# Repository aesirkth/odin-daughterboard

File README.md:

# daughterboard
Daughterboard design notes:

DB circle dimension: 60 mm, up to 75 mm

Include space for 4-5 spacers around edge of PCB

On one of the sides, add space for the header (pin stack) where all the output connections will go to the rest of the electronics. 

Include through holes for the 2 wires to the battery, (Vcc and GND)

AWG 16 cables (order BLACK cables for GND, RED for Vcc)

2 Inputs from battery pack: 
	Vcc (+9V)
	GND

3 Outputs from daughterboard: 
	+5V to OBC
	+12V to VTx/Camera
	GND

Large holes: 0.086 inches in diameter, 0.085 inches from edges

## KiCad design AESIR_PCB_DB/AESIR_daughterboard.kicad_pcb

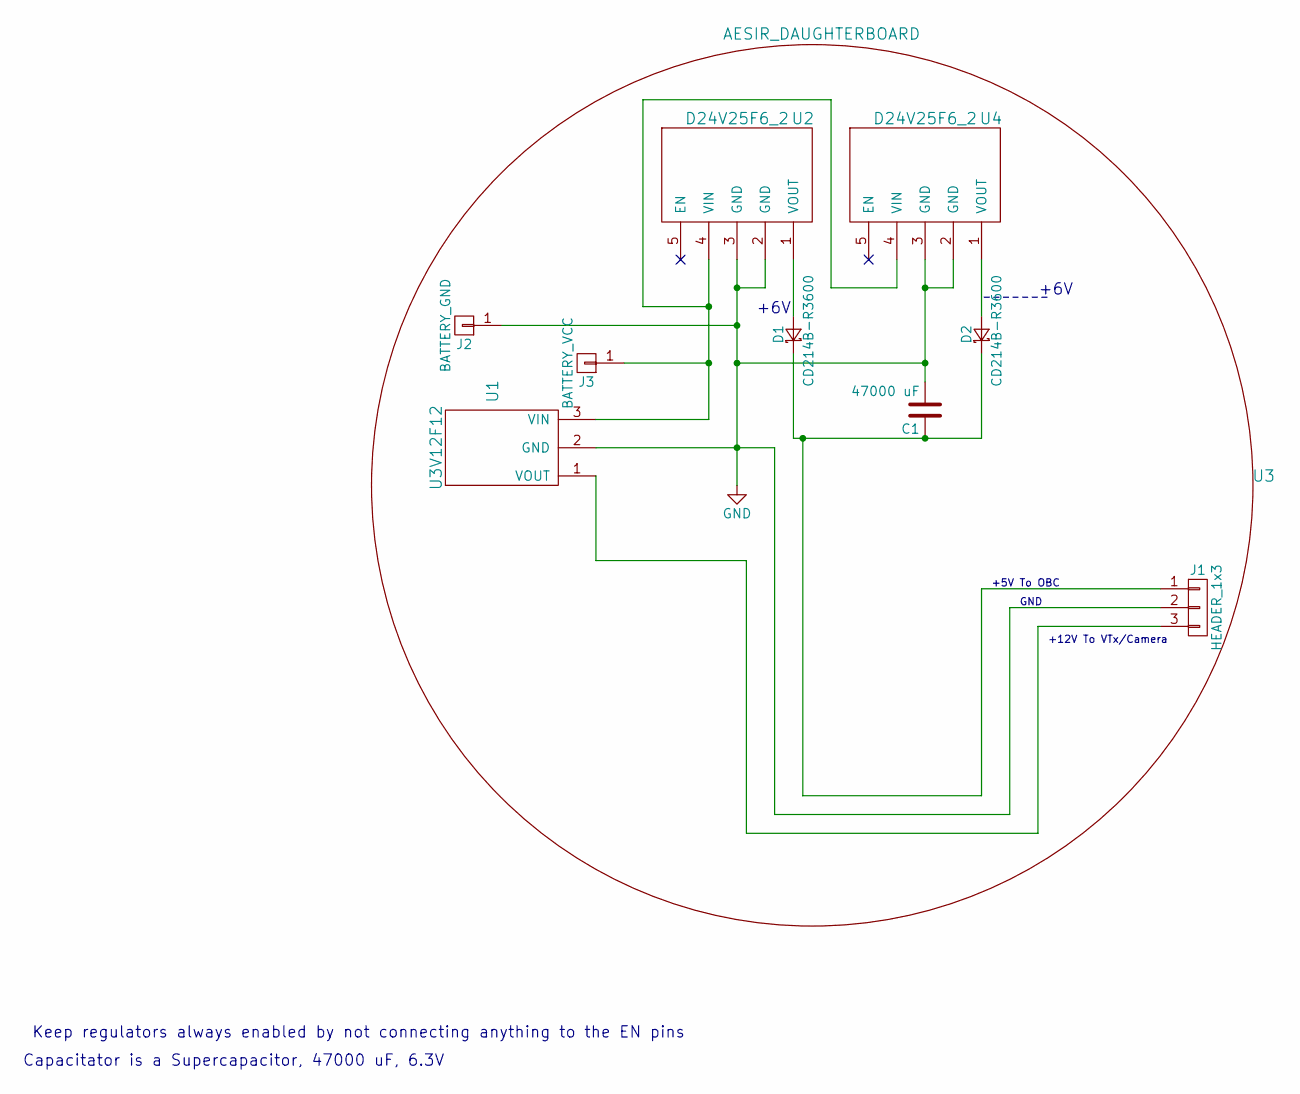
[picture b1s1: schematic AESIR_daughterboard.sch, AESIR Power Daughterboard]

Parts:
C1: 47000 uF; Supercapacitor_Radial
D1, D2: CD214B-R3600; DO-214AA(SMB)
J1: HEADER_1x3; Socket_Strip_Straight_1x03
J2: BATTERY_GND; SolderWirePad_single_1mmDrill
J3: BATTERY_VCC; SolderWirePad_single_1mmDrill
U1: U3V12F12
U2, U4: D24V25F6_2
U3: AESIR_DAUGHTERBOARD; AESIR_DB_OUTLINE_60mm

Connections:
GND: C1.2, J1.2, J2.1, U1.2 (GND), U2.2 (GND), U2.3 (GND), U4.2 (GND), U4.3 (GND)
unnamed: C1.1, D1.1 (K), D2.1 (K), J1.1
unnamed: D1.2 (A), U2.1 (VOUT)
unnamed: D2.2 (A), U4.1 (VOUT)
unnamed: J1.3, U1.1 (VOUT)
unnamed: J3.1, U1.3 (VIN), U2.4 (VIN), U4.4 (VIN)

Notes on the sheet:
+5V To OBC
+12V To VTx/Camera
Keep regulators always enabled by not connecting anything to the EN pins
Capacitator is a Supercapacitor, 47000 uF, 6.3V
+6V
GND

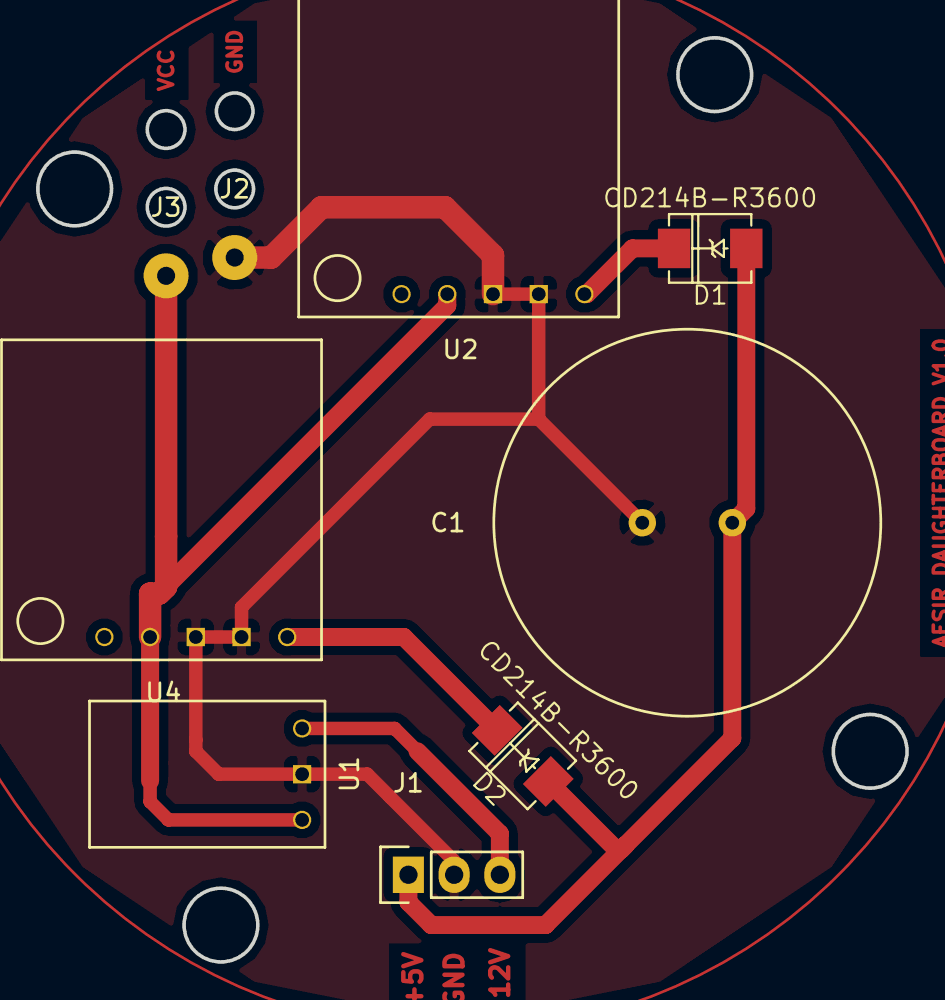
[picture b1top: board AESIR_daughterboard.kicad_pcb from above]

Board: 2 copper layers, 48.3 x 51.3 mm, 10 parts (0 on the bottom side), 6 nets.

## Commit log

2017-11-01 added footprint, Cu outline, schematic, and notes
2017-11-01 added KiCad project files
2017-11-01 added component library
2017-11-01 added gitignore
2017-11-01 removed DS_Store
